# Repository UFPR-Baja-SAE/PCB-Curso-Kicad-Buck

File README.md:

# PCB-Curso-Kicad-Buck
PCB do curso de Kicad da SEATEL 2023 Buck Converter
Design de uma PCB utilizando o LM7805 para fazer um buck converter. 
Este projeto foi utilizado como base para o curso de KiCad da Equipe UFPR BAJA SAE, o projeto de schematic e pcb são inspirados e baseados no projeto de João Alves, especificamente o CSEduino V4. Link para a fonte https://jpralves.net/pages/cseduinoworld.html

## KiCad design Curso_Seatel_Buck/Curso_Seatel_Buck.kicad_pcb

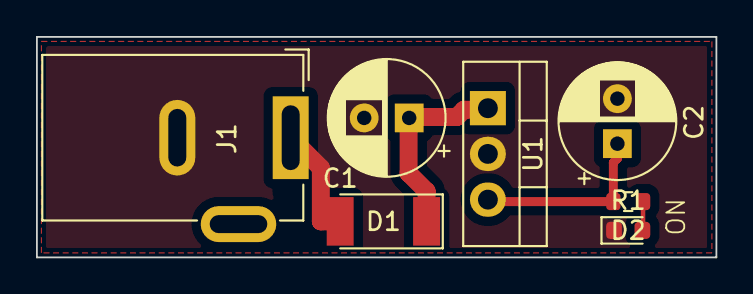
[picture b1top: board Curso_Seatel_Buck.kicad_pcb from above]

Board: 2 copper layers, 37.8 x 12.2 mm, 7 parts (0 on the bottom side), 5 nets.

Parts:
C1, C2: 100nF; CP_Radial_D6.3mm_P2.50mm
D1: SM4001; D_MELF
D2: LED; LED_0603_1608Metric
J1: Barrel_Jack_MountingPin; BarrelJack_GCT_DCJ200-10-A_Horizontal
R1: R; R_0603_1608Metric
U1: LM7805_TO220; TO-220-3_Vertical

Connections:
+5V: C2.1, R1.1, U1.3 (VO)
GND: C1.2, C2.2, D2.1 (K), J1.2, U1.2 (GND)
unnamed: C1.1, D1.1 (K), U1.1 (VI)
unnamed: D1.2 (A), J1.1
unnamed: D2.2 (A), R1.2

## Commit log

2023-05-21 Criado o README.md
    Breve Readme para publicar o repositorio
